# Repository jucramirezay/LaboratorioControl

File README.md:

# LaboratorioControl
Repositorio del laboratorio de control, contiene los códigos para el funcionamiento del laboratorio, descargar la carpeta, separar las guías y los códigos del Arduino y NodeMCU y ejecutar el archivo broker.js que se encuentra en la carpeta "servidor" con el comando "node broker.js".

El servidor contiene una serie de frameworks y paquetes en uso, sin embargo, lo mejor para el usuario es instalarlos por cuenta propia, ya que las versiones pueden variar en gran medida. 

Para instalar los paquetes basta con utilizar el comando. 

npm install nombrePaquete --save

En muchos casos es necesario el uso del super usuario (sudo) para realizar la instalación de manera correcta. La instalación se debe realizar en la carpeta raiz del servidor, es decir, la caperta donde esta ubicado el archivo broker.js. A continuación se brinda el ejemplo de como instalar los paquetes utilizados en el servidor.

sudo npm install chart.js --save \\
sudo npm install ejs --save \\
sudo npm install express --save \\
sudo npm install mosca --save \\
sudo npm install mqtt --save \\
sudo npm install socket.io --save \\

Estos paquete se instalan en una carpeta llamada node_modules, la cual se ubica en la carpeta donde se realizó la instalación. 

Se tienen los códigos del Arduino y del NodeMCU para cada experimento. 

Para la impresión del circuito, el archivo que se debe abrir en kicad (o en algún otro visor de pcb) es el denominado Tesis2.2.

Finalmente, se anexan dos guías, una para el uso del laboratorio, explicando brevemente el objetivo de cada experimento, su funcionamiento y la manera de utilizar la interfaz gráfica. La segunda guía indica como anexar un nuevo experimento, demostrando así la escalabilidad del laboratorio.

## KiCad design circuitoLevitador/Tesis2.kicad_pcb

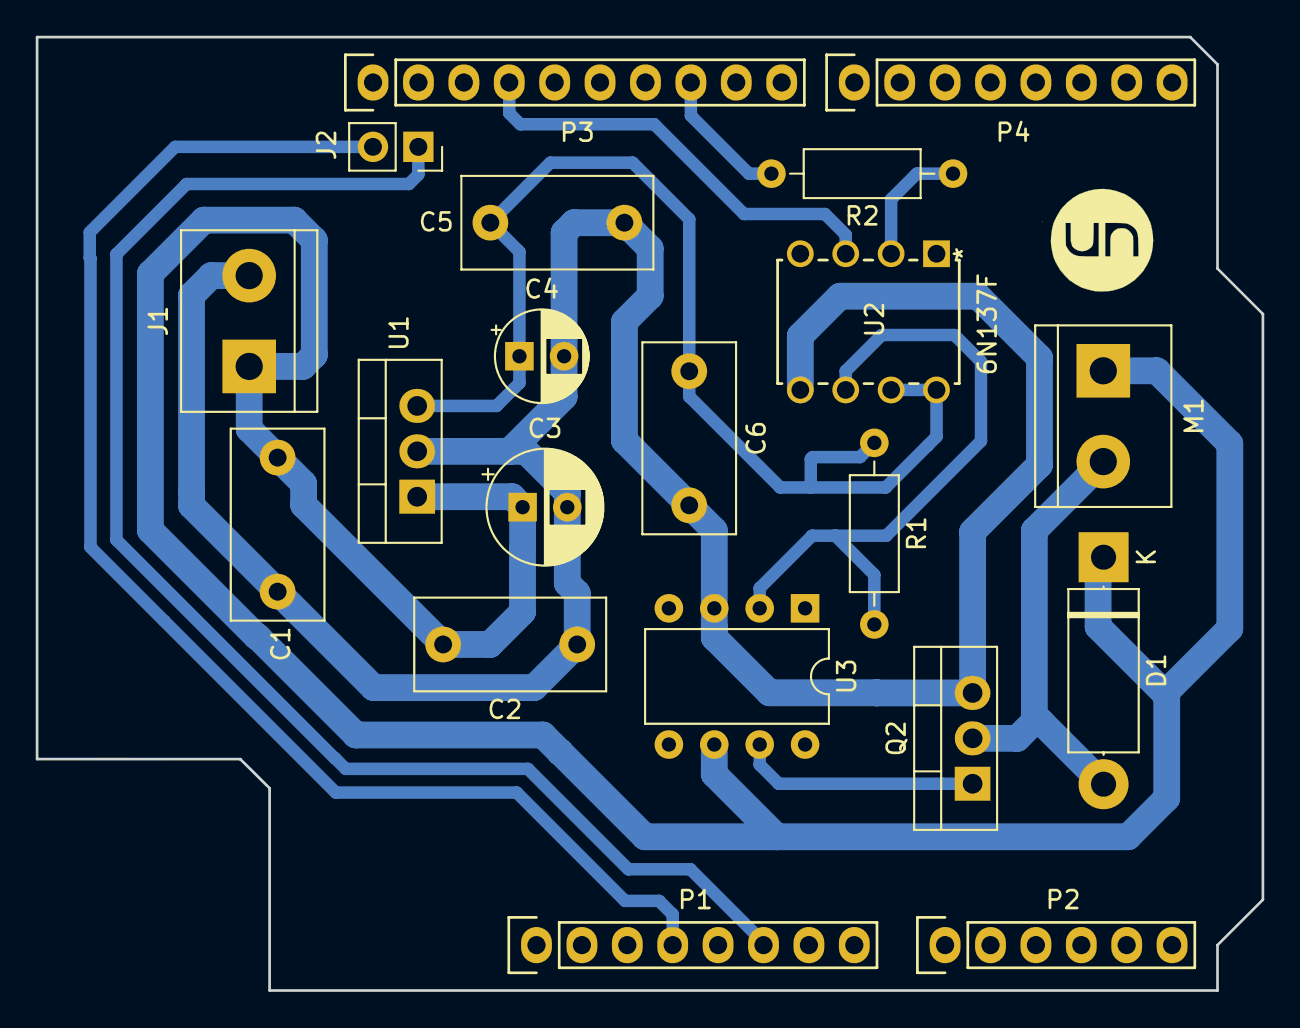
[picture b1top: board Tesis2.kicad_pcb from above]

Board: 2 copper layers, 68.6 x 53.3 mm, 20 parts (0 on the bottom side), 11 nets.

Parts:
C1: 47nF; C_Disc_D10.5mm_W5.0mm_P7.50mm
C2: 470nF; C_Disc_D10.5mm_W5.0mm_P7.50mm
C3: 470uF; CP_Radial_D6.3mm_P2.50mm
C4: 100uF; CP_Radial_D5.0mm_P2.50mm
C5: 100nF; C_Disc_D10.5mm_W5.0mm_P7.50mm
C6: 10nF; C_Disc_D10.5mm_W5.0mm_P7.50mm
D1: D; D_5W_P12.70mm_Horizontal
J1: Fuente; TerminalBlock_bornier-2_P5.08mm
J2: ASensor2; PinSocket_1x02_P2.54mm_Vertical
M1: Fan; TerminalBlock_bornier-2_P5.08mm
P1: Power; Socket_Strip_Arduino_1x08
P2: Analog; Socket_Strip_Arduino_1x06
P3: Digital; Socket_Strip_Arduino_1x10
P4: Digital; Socket_Strip_Arduino_1x08
Q2: IRF630; TO-220-3_Vertical
R1, R2: 220; R_Axial_DIN0207_L6.3mm_D2.5mm_P10.16mm_Horizontal
U1: L7805; TO-220-3_Vertical
U2: 6N137F
U3: MC33152; DIP-8_W7.62mm

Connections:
+3V3: J2.2, P1.4
+12V: C1.1, C2.1, C3.1, D1.1, J1.1, M1.1, U1.1, U3.6
/10(**/SS): P3.8, R2.2
GNDPWR: C1.2, C2.2, C3.2, C4.2, C5.2, C6.2, J1.2, Q2.3, U1.2, U2.5, U3.3
unnamed: C4.1, C5.1, C6.1, R1.1, U1.3, U2.7, U2.8
unnamed: D1.2, M1.2, Q2.2
unnamed: J2.1, P1.6
unnamed: P3.4, U2.3
unnamed: Q2.1, U3.7
unnamed: R1.2, U2.6, U3.2
unnamed: R2.1, U2.2

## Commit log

2020-02-12 Create Levitador
2020-02-12 Create Tanque
2020-02-12 Create explicacion
2020-02-12 Create asd
2020-02-12 Create asdd
2020-02-12 Create as
2020-02-12 Create s
2020-02-12 Create a
2020-02-13 Create aa

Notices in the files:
parts and their libraries:
Copyright 2016 Accelerated Designs. All rights reserved.
